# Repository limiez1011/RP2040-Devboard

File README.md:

# RP2040-Devboard
Basic devboard with rp2040 MCU and 2.54mm headers.

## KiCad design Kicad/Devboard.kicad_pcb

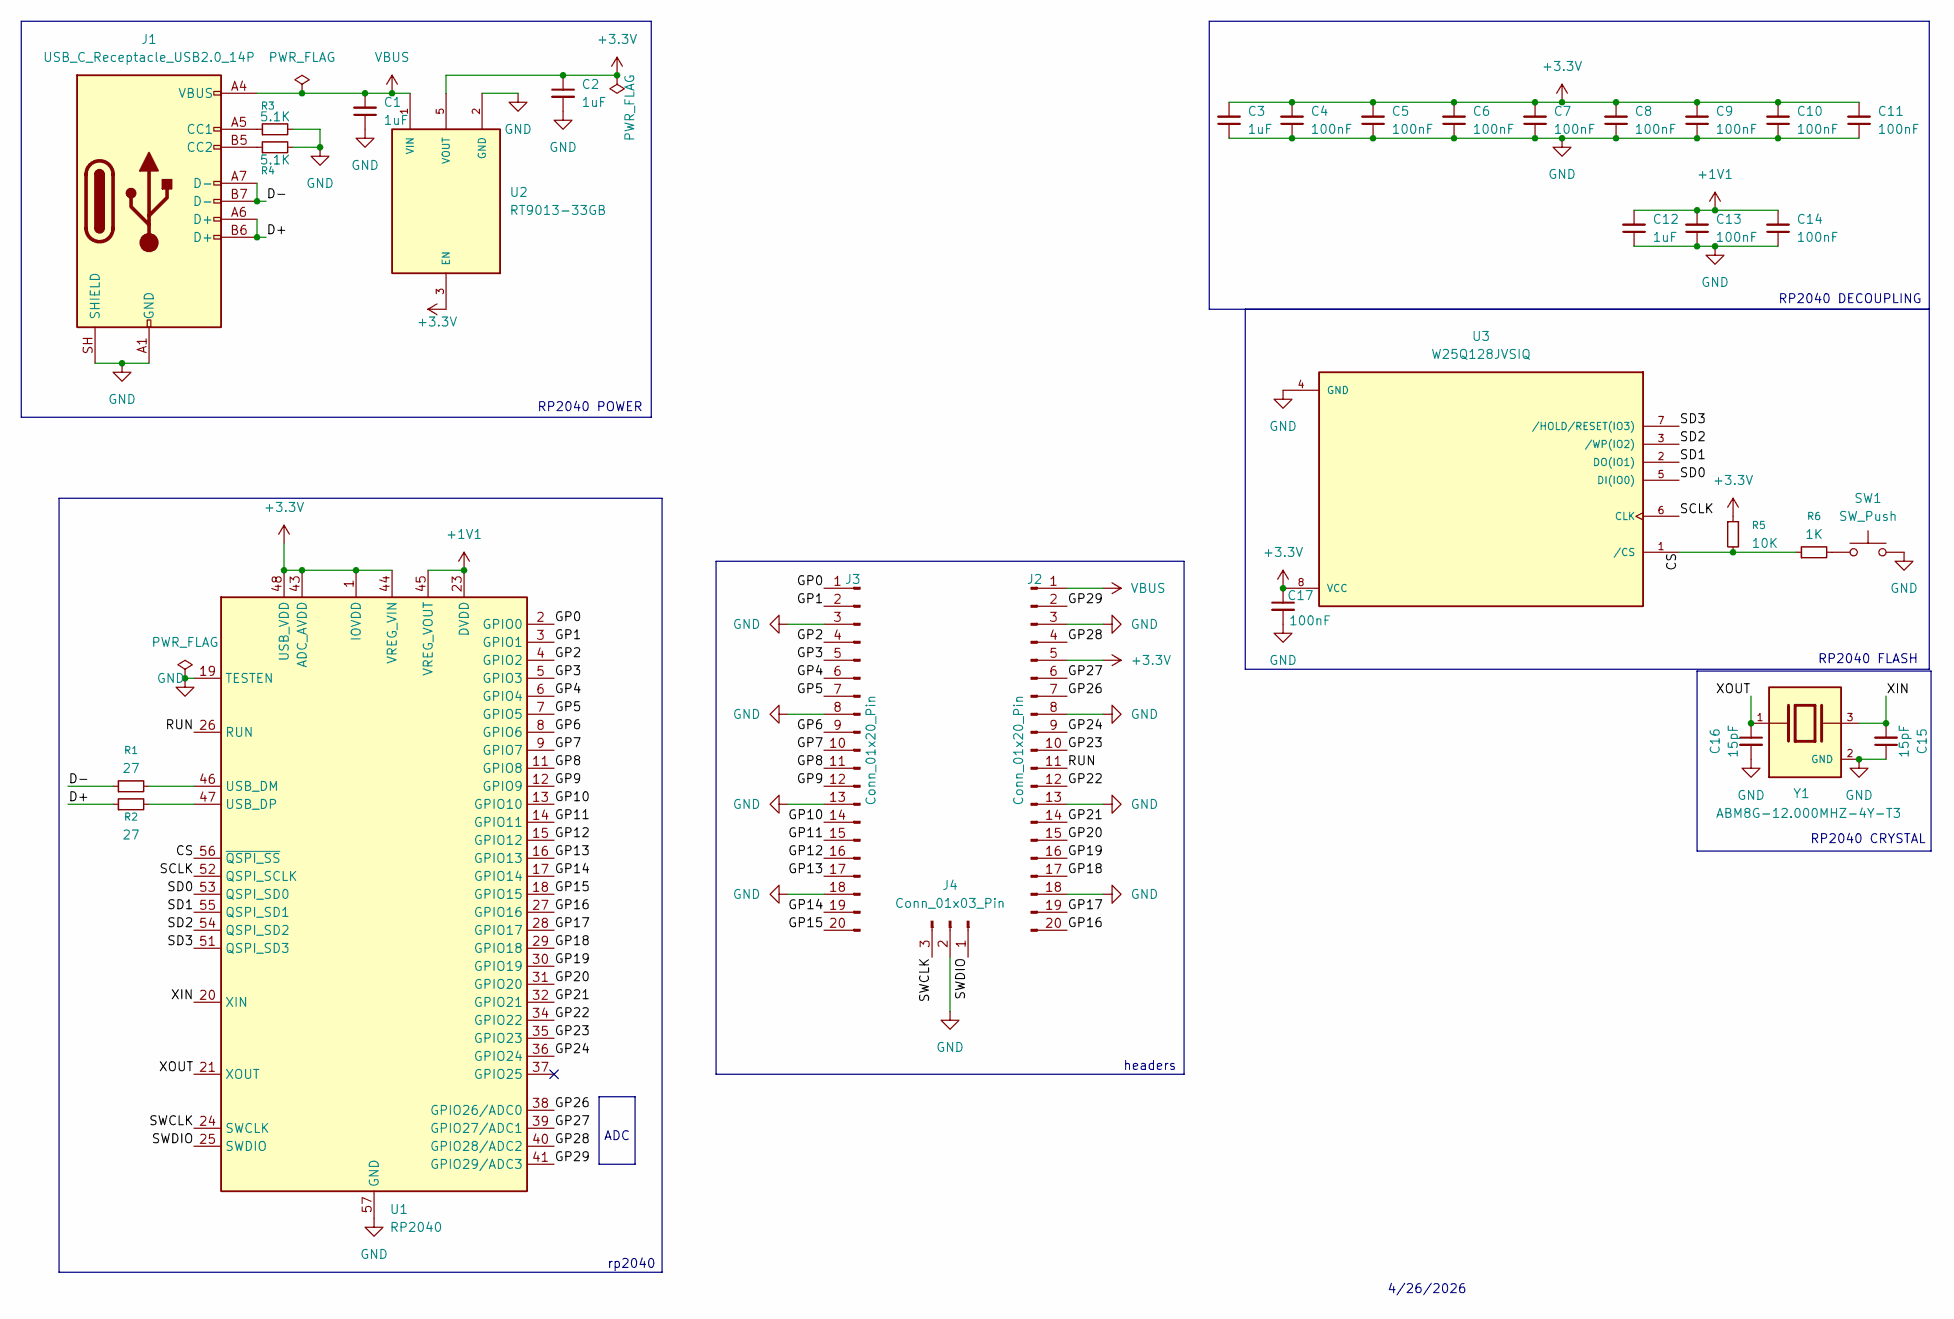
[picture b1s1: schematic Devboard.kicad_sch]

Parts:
C1, C2: 1uF; C_0603_1608Metric
C3, C12: 1uF; C_0402_1005Metric
C4, C5, C6, C7, C8, C9, C10, C11, C13, C14, C17: 100nF; C_0402_1005Metric
C15, C16: 15pF; C_0402_1005Metric
J1: USB_C_Receptacle_USB2.0_14P; USB_C_Receptacle_HRO_TYPE-C-31-M-12
J2, J3: Conn_01x20_Pin; PinHeader_1x20_P2.54mm_Vertical
J4: Conn_01x03_Pin; PinHeader_1x03_P2.54mm_Vertical
R1, R2: 27; R_0402_1005Metric
R3, R4: 5.1K; R_0402_1005Metric
R5: 10K; R_0402_1005Metric
R6: 1K; R_0402_1005Metric
SW1: SW_Push; SW_TS-1088-AR02016
U1: RP2040; QFN-56-1EP_7x7mm_P0.4mm_EP3.2x3.2mm
U2: RT9013-33GB; SOT94P279X129-5N; PARTREV Aprill 2011
U3: W25Q128JVSIQ; Winbond_USON-8-1EP_3x2mm_P0.5mm_EP0.2x1.6mm; PARTREV I
Y1: ABM8G-12.000MHZ-4Y-T3; XTAL_ABM8G-12.000MHZ-4Y-T3; PARTREV 08.13.15

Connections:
+1V1: C12.2, C13.2, C14.2, U1.23 (DVDD), U1.45 (VREG_VOUT), U1.50 (DVDD)
+3.3V: C2.1, C3.2, C4.2, C5.2, C6.2, C7.2, C8.2, C9.2, C10.2, C11.2, C17.1, J2.5, R5.1, U1.1 (IOVDD), U1.10 (IOVDD), U1.22 (IOVDD), U1.33 (IOVDD), U1.42 (IOVDD), U1.43 (ADC_AVDD), U1.44 (VREG_VIN), U1.48 (USB_VDD), U1.49 (IOVDD), U2.3 (EN), U2.5 (VOUT), U3.8 (VCC)
/CS: R5.2, R6.1, U1.56 (~QSPI_SS), U3.1 (/CS)
/D+: J1.A6 (D+), J1.B6 (D+), R2.1
/D-: J1.A7 (D-), J1.B7 (D-), R1.1
/GP0: J3.1, U1.2 (GPIO0)
/GP1: J3.2, U1.3 (GPIO1)
/GP2: J3.4, U1.4 (GPIO2)
/GP3: J3.5, U1.5 (GPIO3)
/GP4: J3.6, U1.6 (GPIO4)
/GP5: J3.7, U1.7 (GPIO5)
/GP6: J3.9, U1.8 (GPIO6)
/GP7: J3.10, U1.9 (GPIO7)
/GP8: J3.11, U1.11 (GPIO8)
/GP9: J3.12, U1.12 (GPIO9)
/GP10: J3.14, U1.13 (GPIO10)
/GP11: J3.15, U1.14 (GPIO11)
/GP12: J3.16, U1.15 (GPIO12)
/GP13: J3.17, U1.16 (GPIO13)
/GP14: J3.19, U1.17 (GPIO14)
/GP15: J3.20, U1.18 (GPIO15)
/GP16: J2.20, U1.27 (GPIO16)
/GP17: J2.19, U1.28 (GPIO17)
/GP18: J2.17, U1.29 (GPIO18)
/GP19: J2.16, U1.30 (GPIO19)
/GP20: J2.15, U1.31 (GPIO20)
/GP21: J2.14, U1.32 (GPIO21)
/GP22: J2.12, U1.34 (GPIO22)
/GP23: J2.10, U1.35 (GPIO23)
/GP24: J2.9, U1.36 (GPIO24)
/GP26: J2.7, U1.38 (GPIO26/ADC0)
/GP27: J2.6, U1.39 (GPIO27/ADC1)
/GP28: J2.4, U1.40 (GPIO28/ADC2)
/GP29: J2.2, U1.41 (GPIO29/ADC3)
/RUN: J2.11, U1.26 (RUN)
/SCLK: U1.52 (QSPI_SCLK), U3.6 (CLK)
/SD0: U1.53 (QSPI_SD0), U3.5 (DI(IO0))
/SD1: U1.55 (QSPI_SD1), U3.2 (DO(IO1))
/SD2: U1.54 (QSPI_SD2), U3.3 (/WP(IO2))
/SD3: U1.51 (QSPI_SD3), U3.7 (/HOLD/RESET(IO3))
/SWCLK: J4.3, U1.24 (SWCLK)
/SWDIO: J4.1, U1.25 (SWDIO)
/XIN: C15.2, U1.20 (XIN), Y1.3
/XOUT: C16.1, U1.21 (XOUT), Y1.1
GND: C1.1, C2.2, C3.1, C4.1, C5.1, C6.1, C7.1, C8.1, C9.1, C10.1, C11.1, C12.1, C13.1, C14.1, C15.1, C16.2, C17.2, J1.A1 (GND), J1.A12 (GND), J1.B1 (GND), J1.B12 (GND), J1.SH (SHIELD), J2.3, J2.8, J2.13, J2.18, J3.3, J3.8, J3.13, J3.18, J4.2, R3.2, R4.2, SW1.2, U1.19 (TESTEN), U1.57 (GND), U2.2 (GND), U3.4 (GND), U3.9, Y1.2 (GND), Y1.4 (GND)
unnamed: J1.A5 (CC1), R3.1
unnamed: J1.B5 (CC2), R4.1
unnamed: R6.2, SW1.1
unnamed: R1.2, U1.46 (USB_DM)
unnamed: R2.2, U1.47 (USB_DP)
VBUS: C1.2, J1.A4 (VBUS), J1.A9 (VBUS), J1.B4 (VBUS), J1.B9 (VBUS), J2.1, U2.1 (VIN)

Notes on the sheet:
RP2040 POWER
rp2040
RP2040 CRYSTAL
ADC
headers
RP2040 DECOUPLING
4/26/2026
RP2040 FLASH

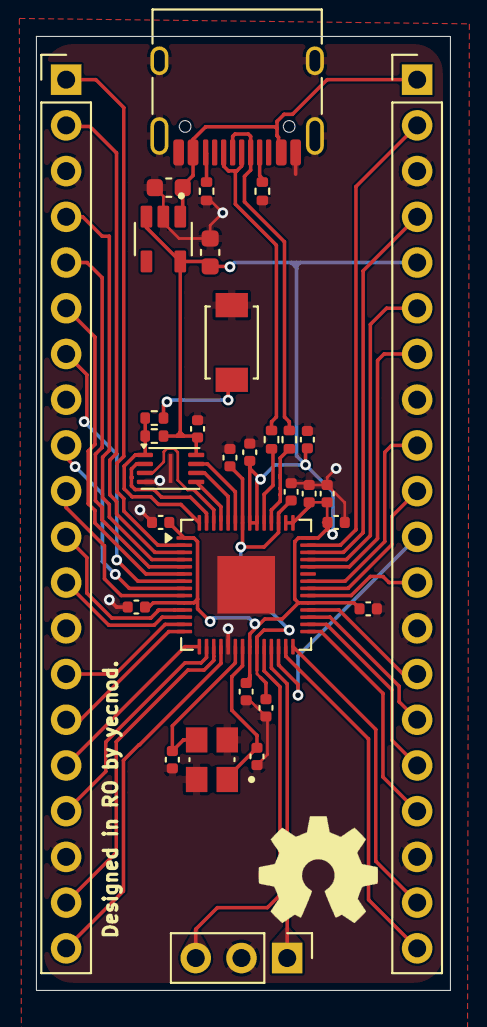
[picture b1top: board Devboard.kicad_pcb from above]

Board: 2 copper layers, 23.0 x 53.0 mm, 32 parts (0 on the bottom side), 51 nets.

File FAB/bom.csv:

Designator,Footprint,Quantity,Value,LCSC Part #
"C1, C2",603,2,1uF,C15849
"C10, C11, C13, C14, C17, C4, C5, C6, C7, C8, C9",402,11,100nF,C1525
"C12, C3",402,2,1uF,C52923
"C15, C16",402,2,15pF,C1548
J1,USB_C_Receptacle_HRO_TYPE-C-31-M-12,1,USB_C_Receptacle_USB2.0_14P,C165948
"R1, R2",402,2,27,C25100
"R3, R4",402,2,5.1K,C25905
R5,402,1,10K,C25744
R6,402,1,1K,C11702
SW1,SW_TS-1088-AR02016,1,SW_Push,C720477
U1,QFN-56-1EP_7x7mm_P0.4mm_EP3.2x3.2mm,1,RP2040,C2040
U2,SOT94P279X129-5N,1,RT9013-33GB,C47773
U3,Winbond_USON-8-1EP_3x2mm_P0.5mm_EP0.2x1.6mm,1,W25Q128JVSIQ,C2986331
Y1,XTAL_ABM8G-12.000MHZ-4Y-T3,1,ABM8G-12.000MHZ-4Y-T3,C596905

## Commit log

2026-04-27 Create ,
2026-04-27 Add images to README for better visualization
    Added images to enhance the README with visual references.
